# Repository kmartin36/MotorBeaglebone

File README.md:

# MotorBeaglebone
Motor drive cape for the Beaglebone Black featuring three channels, encoders, current sensors, and voltage sensing

This uses the High-Res PWM modules, the ADC, and the Enhanced Quadrature Encoder inputs.

See [this](https://github.com/Teknoman117/beaglebot/tree/master/encoders) repo for information on using the EQEP modules.

The new version is designed in kicad which features six channels and makes use of the DRV8873 motor driver IC. The three remaining quadrature encoder channels routed to the PRU pins for software decoding.

There is also a design based on the PocketBeagle with only four motors as the PocketBeagle only provies four of the 6 PWM modules on header pins.

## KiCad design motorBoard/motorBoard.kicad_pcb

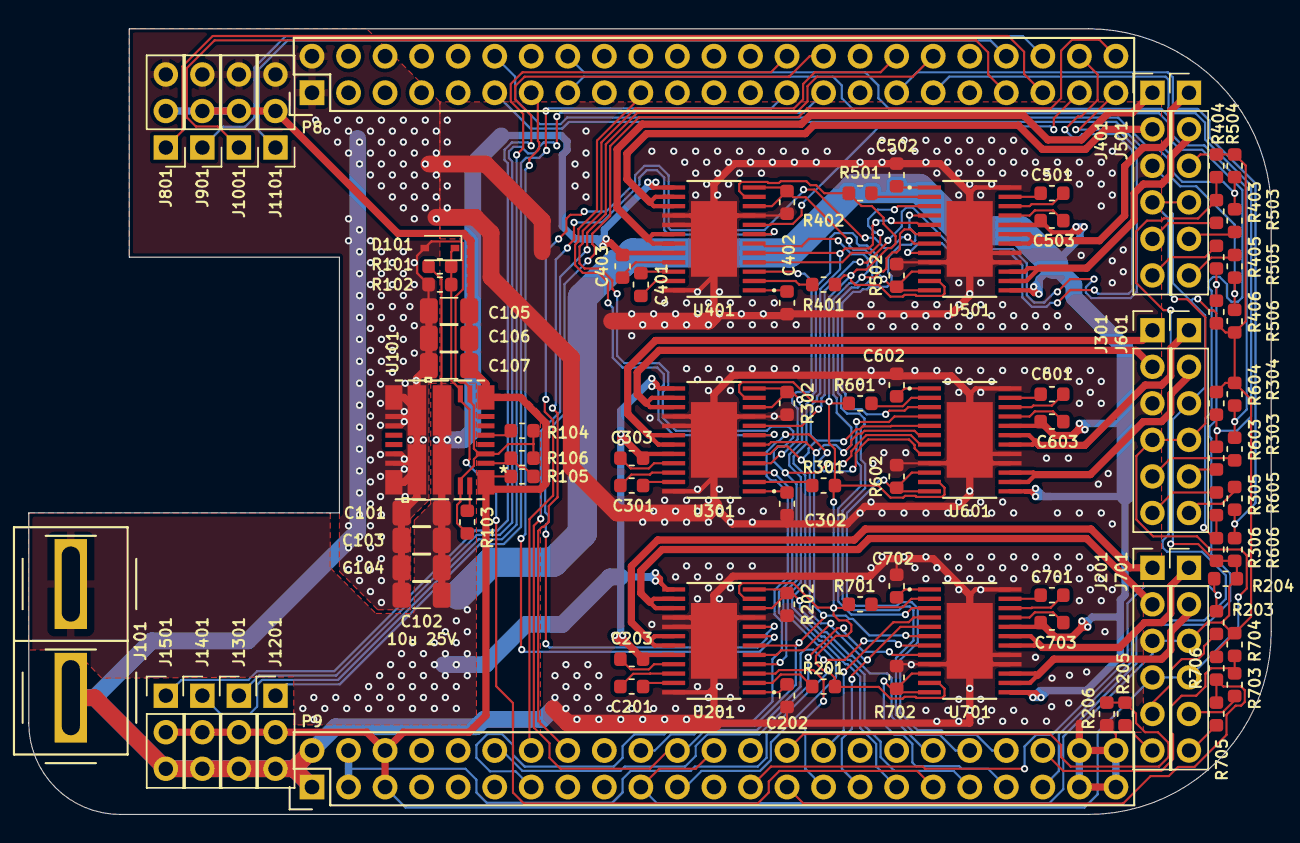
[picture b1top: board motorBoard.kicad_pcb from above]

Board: 2 copper layers, 86.4 x 54.6 mm, 92 parts (0 on the bottom side), 109 nets.

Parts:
C101, C102, C103, C104: 10u 25V; C_1206_3216Metric
C105, C106, C107: 47u 6V3; C_1206_3216Metric
C201, C301, C401, C501, C601, C701: 47n; C_0603_1608Metric
C202, C302, C402, C502, C602, C702: 1u; C_0603_1608Metric
C203, C303, C403, C503, C603, C703: 0u1; C_0603_1608Metric
D101: 1V8; D_SOD-323
J101: Conn_01x02_Male; 45A-VERT-PAIR
J201, J301, J401, J501, J601, J701: CONN_01X06; PinHeader_1x06_P2.54mm_Vertical
J801, J901, J1001, J1101, J1201, J1301, J1401, J1501: Conn_01x03; PinHeader_1x03_P2.54mm_Vertical
P8: P8; Socket_BeagleBone_Black
P9: P9; Socket_BeagleBone_Black
R101: 68k1; R_0603_1608Metric
R102: 7k5; R_0603_1608Metric
R103: 40k2; R_0603_1608Metric
R104: 4k42; R_0603_1608Metric
R105, R201, R301, R401, R501, R601, R701: 10k; R_0603_1608Metric
R106: 1k37; R_0603_1608Metric
R202, R302, R402, R502, R602, R702: 196; R_0603_1608Metric
R203, R205, R303, R305, R403, R405, R503, R505, R603, R605, R703, R705: RA; R_0603_1608Metric
R204, R206, R304, R306, R404, R406, R504, R506, R604, R606, R704, R706: RB; R_0603_1608Metric
U101: TPSM84824; MOL-24
U201, U301, U401, U501, U601, U701: DRV8873; PWP-HTSSOP-24

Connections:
+3V3: P9.3, P9.4, R201.1, R301.1, R401.1, R501.1, R601.1, R701.1, U201.11 (nSLEEP), U301.11 (nSLEEP), U401.11 (nSLEEP), U501.11 (nSLEEP), U601.11 (nSLEEP), U701.11 (nSLEEP)
+5V: C105.1, C106.1, C107.1, J201.4, J301.4, J401.4, J501.4, J601.4, J701.4, J801.2, J901.2, J1001.2, J1101.2, J1201.2, J1301.2, J1401.2, J1501.2, P9.5, P9.6, R105.1, U101.1 (VOUT), U101.8 (VOUT)
+BATT: C101.1, C102.1, C103.1, C104.1, C203.2, C303.2, C403.2, C503.2, C603.2, C703.2, J101.2, R101.1, U101.11 (VIN), U101.22 (VIN), U201.13 (VM), U201.20 (VM), U301.13 (VM), U301.20 (VM), U401.13 (VM), U401.20 (VM), U501.13 (VM), U501.20 (VM), U601.13 (VM), U601.20 (VM), U701.13 (VM), U701.20 (VM)
/Motor0/MISO: U601.4 (SDI), U701.3 (SDO)
/Motor1/MISO: U501.4 (SDI), U601.3 (SDO)
/Motor2/MISO: U401.4 (SDI), U501.3 (SDO)
/Motor3/MISO: U301.4 (SDI), U401.3 (SDO)
/Motor4/MISO: U201.4 (SDI), U301.3 (SDO)
ADC0: P9.39, R702.1, U701.10 (IPROPI1), U701.12 (IPROPI2)
ADC1: P9.40, R602.1, U601.10 (IPROPI1), U601.12 (IPROPI2)
ADC2: P9.37, R502.1, U501.10 (IPROPI1), U501.12 (IPROPI2)
ADC3: P9.38, R402.1, U401.10 (IPROPI1), U401.12 (IPROPI2)
ADC4: P9.33, R302.1, U301.10 (IPROPI1), U301.12 (IPROPI2)
ADC5: P9.36, R202.1, U201.10 (IPROPI1), U201.12 (IPROPI2)
DIR0: P9.12, U701.8 (PH/IN2)
DIR1: P9.13, U601.8 (PH/IN2)
DIR2: P8.44, U501.8 (PH/IN2)
DIR3: P8.43, U401.8 (PH/IN2)
DIR4: P8.45, U301.8 (PH/IN2)
DIR5: P8.46, U201.8 (PH/IN2)
GNDD: C101.2, C102.2, C103.2, C104.2, C105.2, C106.2, C107.2, C202.2, C302.2, C402.2, C502.2, C602.2, C702.2, D101.2 (A), J101.1, J201.3, J301.3, J401.3, J501.3, J601.3, J701.3, J801.3, J901.3, J1001.3, J1101.3, J1201.3, J1301.3, J1401.3, J1501.3, P8.1, P8.2, P9.1, P9.2, P9.43, P9.44, P9.45, P9.46, R102.2, R103.2, R104.2, R106.2, R202.2, R204.2, R206.2, R302.2, R304.2, R306.2, R402.2, R404.2, R406.2, R502.2, R504.2, R506.2, R602.2, R604.2, R606.2, R702.2, R704.2, R706.2, U101.3 (AGND), U101.9 (AGND), U101.12 (PGND), U101.13 (PGND), U101.14 (PGND), U101.15 (PGND), U101.18 (PGND), U101.19 (PGND), U101.20 (PGND), U101.21 (PGND), U101.23 (AGND), U201.9 (DISABLE), U201.16 (SRC), U201.17 (SRC), U201.24 (GND), U201.25 (GND), U301.9 (DISABLE), U301.16 (SRC), U301.17 (SRC), U301.24 (GND), U301.25 (GND), U401.9 (DISABLE), U401.16 (SRC), U401.17 (SRC), U401.24 (GND), U401.25 (GND), U501.9 (DISABLE), U501.16 (SRC), U501.17 (SRC), U501.24 (GND), U501.25 (GND), U601.9 (DISABLE), U601.16 (SRC), U601.17 (SRC), U601.24 (GND), U601.25 (GND), U701.9 (DISABLE), U701.16 (SRC), U701.17 (SRC), U701.24 (GND), U701.25 (GND)
MISO: P9.29, U201.3 (SDO)
MOSI: P9.30, U701.4 (SDI)
unnamed: C201.1, U201.22 (CPH)
unnamed: C201.2, U201.23 (CPL)
unnamed: C202.1, U201.1 (DVDD)
unnamed: C203.1, U201.21 (VCP)
unnamed: C301.1, U301.22 (CPH)
unnamed: C301.2, U301.23 (CPL)
unnamed: C302.1, U301.1 (DVDD)
unnamed: C303.1, U301.21 (VCP)
unnamed: C401.1, U401.22 (CPH)
unnamed: C401.2, U401.23 (CPL)
unnamed: C402.1, U401.1 (DVDD)
unnamed: C403.1, U401.21 (VCP)
unnamed: C501.1, U501.22 (CPH)
unnamed: C501.2, U501.23 (CPL)
unnamed: C502.1, U501.1 (DVDD)
unnamed: C503.1, U501.21 (VCP)
unnamed: C601.1, U601.22 (CPH)
unnamed: C601.2, U601.23 (CPL)
unnamed: C602.1, U601.1 (DVDD)
unnamed: C603.1, U601.21 (VCP)
unnamed: C701.1, U701.22 (CPH)
unnamed: C701.2, U701.23 (CPL)
unnamed: C702.1, U701.1 (DVDD)
unnamed: C703.1, U701.21 (VCP)
unnamed: J201.1, U201.18 (OUT1), U201.19 (OUT1)
unnamed: J201.2, U201.14 (OUT2), U201.15 (OUT2)
unnamed: J201.5, R203.1
unnamed: J201.6, R205.1
unnamed: J301.1, U301.18 (OUT1), U301.19 (OUT1)
unnamed: J301.2, U301.14 (OUT2), U301.15 (OUT2)
unnamed: J301.5, R303.1
unnamed: J301.6, R305.1
unnamed: J401.1, U401.18 (OUT1), U401.19 (OUT1)
unnamed: J401.2, U401.14 (OUT2), U401.15 (OUT2)
unnamed: J401.5, R403.1
unnamed: J401.6, R405.1
unnamed: J501.1, U501.18 (OUT1), U501.19 (OUT1)
unnamed: J501.2, U501.14 (OUT2), U501.15 (OUT2)
unnamed: J501.5, R503.1
unnamed: J501.6, R505.1
unnamed: J601.1, U601.18 (OUT1), U601.19 (OUT1)
unnamed: J601.2, U601.14 (OUT2), U601.15 (OUT2)
unnamed: J601.5, R603.1
unnamed: J601.6, R605.1
unnamed: J701.1, U701.18 (OUT1), U701.19 (OUT1)
unnamed: J701.2, U701.14 (OUT2), U701.15 (OUT2)
unnamed: J701.5, R703.1
unnamed: J701.6, R705.1
unnamed: R103.1, U101.24 (RT/CLK)
unnamed: R104.1, U101.5 (TT)
unnamed: R105.2, R106.1, U101.2 (FB)
unnamed: R201.2, U201.2 (nFAULT)
unnamed: R301.2, U301.2 (nFAULT)
unnamed: R401.2, U401.2 (nFAULT)
unnamed: R501.2, U501.2 (nFAULT)
unnamed: R601.2, U601.2 (nFAULT)
unnamed: R701.2, U701.2 (nFAULT)
SCK: P9.31, U201.5 (SCLK), U301.5 (SCLK), U401.5 (SCLK), U501.5 (SCLK), U601.5 (SCLK), U701.5 (SCLK)
VBATT: D101.1 (K), P9.35, R101.2, R102.1, U101.10 (EN)
eQEP0A: P9.42, R703.2, R704.1
eQEP0B: P9.27, R705.2, R706.1
eQEP1A: P8.35, R603.2, R604.1
eQEP1B: P8.33, R605.2, R606.1
eQEP2A: P8.12, R503.2, R504.1
eQEP2B: P8.11, R505.2, R506.1
nCS: P9.20, U201.6 (nSCS), U301.6 (nSCS), U401.6 (nSCS), U501.6 (nSCS), U601.6 (nSCS), U701.6 (nSCS)
pru0_3: P9.28, R205.2, R206.1
pru0_6: P9.41, R403.2, R404.1
pru0_7: P9.25, R203.2, R204.1
pru0_14: P8.16, R303.2, R304.1
pru0_15: P8.15, R305.2, R306.1
pru0_16: P9.19, P9.24, R405.2, R406.1
pru1_4: J801.1, P8.41
pru1_5: J901.1, P8.42
pru1_6: J1001.1, P8.39
pru1_7: J1101.1, P8.40
pru1_8: J1201.1, P8.27
pru1_9: J1301.1, P8.29
pru1_10: J1401.1, P8.28
pru1_11: J1501.1, P8.30
pwm0A: P8.36, P9.22, U701.7 (EN/IN1)
pwm0B: P8.34, P9.21, U601.7 (EN/IN1)
pwm1A: P9.14, U501.7 (EN/IN1)
pwm1B: P9.16, U401.7 (EN/IN1)
pwm2A: P8.19, U301.7 (EN/IN1)
pwm2B: P8.13, U201.7 (EN/IN1)

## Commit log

2015-03-15 Using CC-BY-SA license
2015-03-15 Adding info to the README file
2015-03-15 Correcting syntax
2019-11-23 Modified P9 to use pins 1-46 instead of 47-92
2019-11-23 New design with DRV8873s and using kicad
2019-11-23 Updated README for the new board designs
2019-11-24 Fixing paths to libraries
2019-11-24 routing
2019-11-27 Routing 1st draft
2019-11-28 Added thermal planes Improved routing Increased width of power traces where possible
2019-11-28 Updated 3D models
2019-11-29 Adding the pin spreadsheet
2019-11-30 Changed pins in schematic 8 servos Fixed paths
2019-12-09 More routing
2019-12-11 Routing 1st pass complete
2019-12-11 Wider traces for power nets
2019-12-28 Wider motor traces
2019-12-28 Cleaning up traces
2020-02-20 Adding python motor control-over-http code
2020-03-17 More space for power traces
2020-07-20 Widened traces for V+ to motor drivers Added VIA stitching to V+ and GND planes V+ trace widths set using +60C, 5A, and 2oz copper
2020-07-20 Widened GND traces to motor drivers GND trace width determined using +60C, 5A, and 2oz copper
2020-07-25 Added top and bottom heatsink planes Added thermal vias between ground planes
2020-07-26 Beginning silkscreen
2020-07-26 Moved silkscreen to B.SilkS layer because silkscreen in libraries cannot be modified Silkscreen 1.0 complete
2020-07-27 Added a few more thermal vias Cleaned up the silkscreen
2020-07-27 Changed capacitor values to include voltage ratings Changed TBD resistors to RA/RB for upper and lower divider resistors
2020-07-27 Improved heatsink area Improved silkscreen
2020-07-27 Modified DRC to OSH Park 2oz requirements Most traces fail DRC
2020-07-27 Adding gerbers
2020-07-27 Moved items to at least 15mil from the outline
2020-07-27 Updated gerbers to latest
2022-07-05 Modified to 6/6 trace/space to allow Oshpark production
2022-09-24 Replaced large vias with 2 normal small vias Reduced via size to 20/10 to match OshPark
2022-09-26 Updated top silkscreen gerber file to indicate that it is the top instead of the bottom

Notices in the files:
parts and their libraries:
Copyright 2016 Accelerated Designs. All rights reserved.
